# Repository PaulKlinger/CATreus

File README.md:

# CATreus

A wireless keyboard based on the Keyboardio Atreus.

* NRF54L15 Bluetooth SoC (HolyIOT module)
* NPM1300 PMIC for battery management
* 14500 li-ion battery (900mAh)
* 128x64 OLED display (SSD13060based)
* 4 status LEDs, 1 charge LED
* 3D printed [case](/case)
* custom [firmware](/kbd_firmware)
* Kailh Midnight Pro Silent Switches
* MAO profile keycaps ([from Aliexpress](https://www.aliexpress.com/item/1005008664883621.html))
* cat animations by John William Bond (u/Kaimatten), [original video](https://www.reddit.com/r/PixelArt/comments/hoxd95/1_minute_of_1_bit_cat_animations)

Key layout is hardcoded in the firware, I'm using a NEO2 based layout.

## Notes

Programmed via the 5 holes on the top next to the leds, using a custom pogo pin connector.
Spacing is 2.54mm, so can just solder pogo pins to a piece of protoboard.
pinout:
```
   NC    RESET   GND
   3V3   SWDIO   SWCLK
```

Wake button is top left of the center 4 buttons, used to wake the keyboard from sleep mode (30min of inactivity).
UI help by pressing wake + H.

CMD & CTRL keys can be swapped with wake + W for use on Windows/Mac this is persisted per bluetooth connection.

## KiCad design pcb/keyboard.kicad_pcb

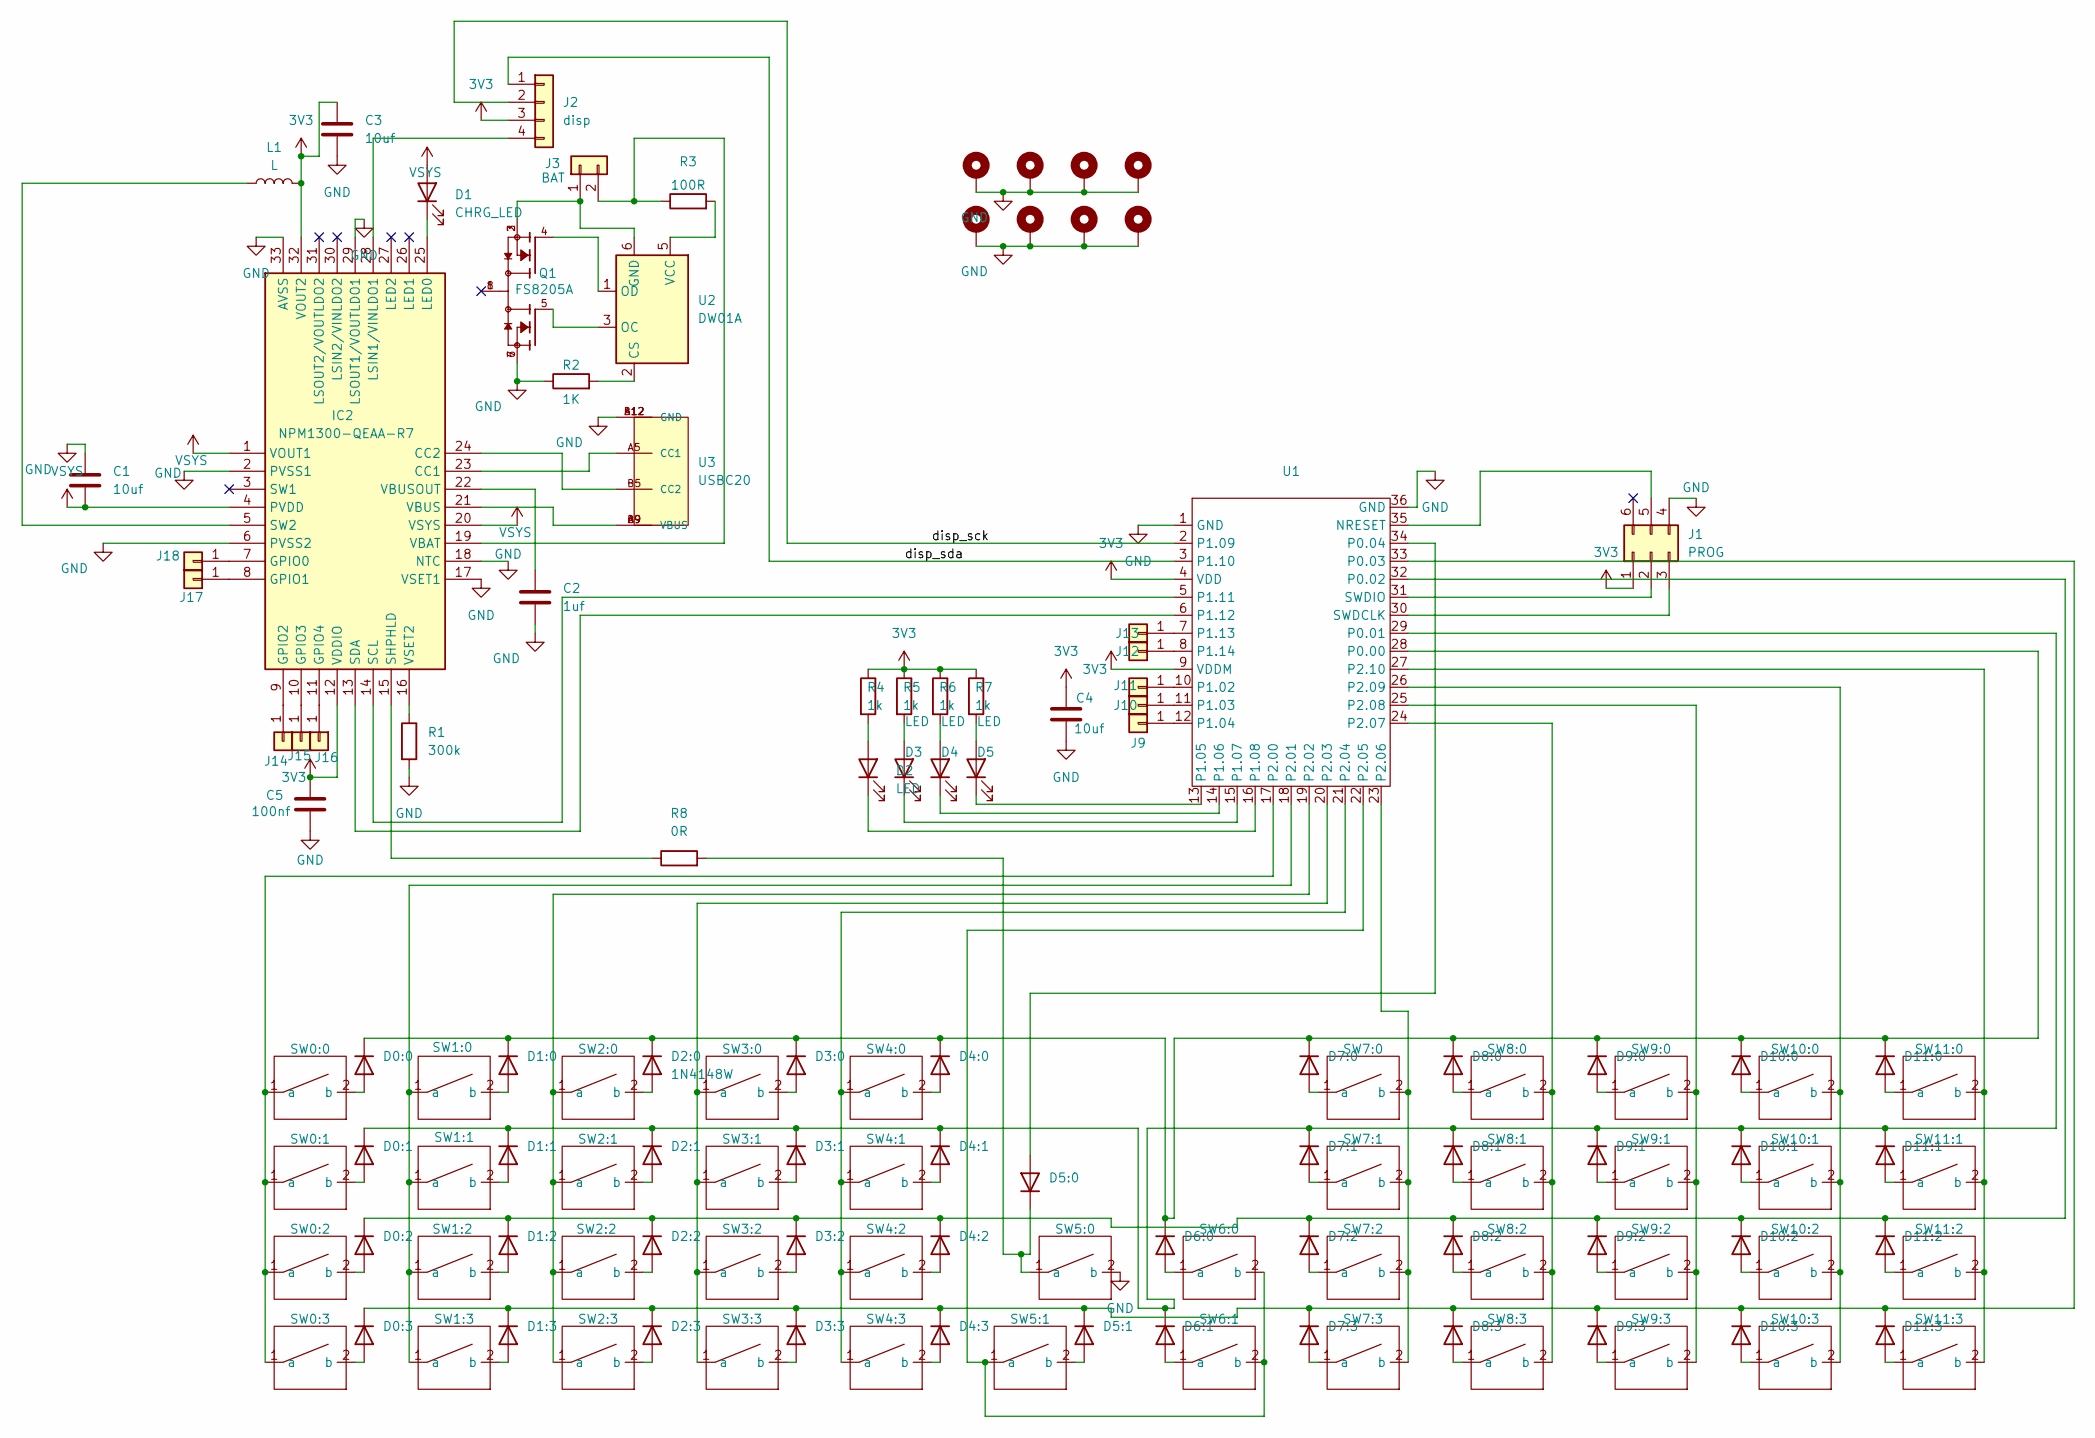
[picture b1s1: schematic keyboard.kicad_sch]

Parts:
C1, C3, C4: 10uf; C_0805_2012Metric_Pad1.18x1.45mm_HandSolder
C2: 1uf; C_0805_2012Metric_Pad1.18x1.45mm_HandSolder
C5: 100nf; C_0805_2012Metric_Pad1.18x1.45mm_HandSolder
D0:0, D0:1, D0:2, D0:3, D1:0, D1:1, D1:2, D1:3, D2:1, D2:2, D2:3, D3:0, D3:1, D3:2, D3:3, D4:0, D4:1, D4:2, D4:3, D5:0, D5:1, D6:0, D6:1, D7:0, D7:1, D7:2, D7:3, D8:0, D8:1, D8:2, D8:3, D9:0, D9:1, D9:2, D9:3, D10:0, D10:1, D10:2, D10:3, D11:0, D11:1, D11:2, D11:3: Nexperia_CFP3_SOD-123W
D1: CHRG_LED; LED_0805_2012Metric_Pad1.15x1.40mm_HandSolder
D2, D3, D4, D5: LED; LED_0805_2012Metric_Pad1.15x1.40mm_HandSolder
D2:0: 1N4148W; D_SOD-123
H1, H2, H3, H4, H5, H6, H7, H8: MountingHole_Pad; MountingHole_2.2mm_M2_DIN965_Pad
IC2: NPM1300-QEAA-R7; QFN50P500X500X90-33N; Mouser Part Number 949-NPM1300-QEAA-R7
J1: PROG; SWD_PROG_5pin
J2: disp; PinHeader_1x04_P2.54mm_Vertical
J3: BAT; PinHeader_1x02_P2.54mm_Vertical
J9, J10, J11, J12, J13, J14, J15, J16, J17, J18: Conn_01x01; SolderWirePad_1x01_SMD_1x2mm
L1: L; L_1008_2520Metric_Pad1.43x2.20mm_HandSolder
Q1: FS8205A; SOP65P640X120-8N; PARTREV 1.7
R1: 300k; R_0805_2012Metric_Pad1.20x1.40mm_HandSolder
R2: 1K; R_0805_2012Metric_Pad1.20x1.40mm_HandSolder
R3: 100R; R_0805_2012Metric_Pad1.20x1.40mm_HandSolder
R4, R5, R6, R7: 1k; R_0805_2012Metric_Pad1.20x1.40mm_HandSolder
R8: 0R; R_0805_2012Metric_Pad1.20x1.40mm_HandSolder
SW0:0, SW0:1, SW0:2, SW0:3, SW1:0, SW1:1, SW1:2, SW1:3, SW2:0, SW2:1, SW2:2, SW2:3, SW3:0, SW3:1, SW3:2, SW3:3, SW4:0, SW4:1, SW4:2, SW4:3, SW5:0, SW5:1, SW6:0, SW6:1, SW7:0, SW7:1, SW7:2, SW7:3, SW8:0, SW8:1, SW8:2, SW8:3, SW9:0, SW9:1, SW9:2, SW9:3, SW10:0, SW10:1, SW10:2, SW10:3, SW11:0, SW11:1, SW11:2, SW11:3: SW_Cherry_MX_PCB
U1: nrf54l15_holyiot
U2: DW01A; SOT-23-6
U3: USBC20; USBC_6PIN

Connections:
3V3: C3.1, C4.1, C5.1, IC2.12 (VDDIO), IC2.32 (VOUT2), J1.1, J2.3, L1.2, R4.1, R5.1, R6.1, R7.1, U1.4 (VDD), U1.9 (VDDM)
/disp_sck: J2.2, U1.2 (P1.09)
/disp_sda: J2.1, U1.3 (P1.10)
GND: C1.1, C2.2, C3.2, C4.2, C5.2, H1.1, H2.1, H3.1, H4.1, H5.1, H6.1, H7.1, H8.1, IC2.2 (PVSS1), IC2.6 (PVSS2), IC2.17 (VSET1), IC2.18 (NTC), IC2.29 (LSOUT1/VOUTLDO1), IC2.33 (AVSS), J1.4, Q1.6, Q1.7, R1.2, R2.1, SW5:0.2 (b), U1.1 (GND), U1.36 (GND), U3.A12 (GND), U3.B12 (GND)
unnamed: D0:0.2 (A), SW0:0.2 (b)
unnamed: D0:0.1 (K), D1:0.1 (K), D2:0.1 (K), D3:0.1 (K), D4:0.1 (K), D6:0.1 (K), D7:0.1 (K), D8:0.1 (K), D9:0.1 (K), D10:0.1 (K), D11:0.1 (K), U1.28 (P0.00)
unnamed: D0:1.2 (A), SW0:1.2 (b)
unnamed: D0:1.1 (K), D1:1.1 (K), D2:1.1 (K), D3:1.1 (K), D4:1.1 (K), D6:1.1 (K), D7:1.1 (K), D8:1.1 (K), D9:1.1 (K), D10:1.1 (K), D11:1.1 (K), U1.29 (P0.01)
unnamed: D0:2.2 (A), SW0:2.2 (b)
unnamed: D0:2.1 (K), D1:2.1 (K), D2:2.1 (K), D3:2.1 (K), D4:2.1 (K), D7:2.1 (K), D8:2.1 (K), D9:2.1 (K), D10:2.1 (K), D11:2.1 (K), U1.32 (P0.02)
unnamed: D0:3.2 (A), SW0:3.2 (b)
unnamed: D0:3.1 (K), D1:3.1 (K), D2:3.1 (K), D3:3.1 (K), D4:3.1 (K), D5:1.1 (K), D7:3.1 (K), D8:3.1 (K), D9:3.1 (K), D10:3.1 (K), D11:3.1 (K), U1.33 (P0.03)
unnamed: D1.1 (K), IC2.25 (LED0)
unnamed: D1:0.2 (A), SW1:0.2 (b)
unnamed: D1:1.2 (A), SW1:1.2 (b)
unnamed: D1:2.2 (A), SW1:2.2 (b)
unnamed: D1:3.2 (A), SW1:3.2 (b)
unnamed: D2.2 (A), R4.2
unnamed: D2.1 (K), U1.16 (P1.08)
unnamed: D2:0.2 (A), SW2:0.2 (b)
unnamed: D2:1.2 (A), SW2:1.2 (b)
unnamed: D2:2.2 (A), SW2:2.2 (b)
unnamed: D2:3.2 (A), SW2:3.2 (b)
unnamed: D3.2 (A), R5.2
unnamed: D3.1 (K), U1.15 (P1.07)
unnamed: D3:0.2 (A), SW3:0.2 (b)
unnamed: D3:1.2 (A), SW3:1.2 (b)
unnamed: D3:2.2 (A), SW3:2.2 (b)
unnamed: D3:3.2 (A), SW3:3.2 (b)
unnamed: D4.2 (A), R6.2
unnamed: D4.1 (K), U1.14 (P1.06)
unnamed: D4:0.2 (A), SW4:0.2 (b)
unnamed: D4:1.2 (A), SW4:1.2 (b)
unnamed: D4:2.2 (A), SW4:2.2 (b)
unnamed: D4:3.2 (A), SW4:3.2 (b)
unnamed: D5.2 (A), R7.2
unnamed: D5.1 (K), U1.13 (P1.05)
unnamed: D5:0.2 (A), U1.34 (P0.04)
unnamed: D5:0.1 (K), R8.2, SW5:0.1 (a)
unnamed: D5:1.2 (A), SW5:1.2 (b)
unnamed: D6:0.2 (A), SW6:0.1 (a)
unnamed: D6:1.2 (A), SW6:1.1 (a)
unnamed: D7:0.2 (A), SW7:0.1 (a)
unnamed: D7:1.2 (A), SW7:1.1 (a)
unnamed: D7:2.2 (A), SW7:2.1 (a)
unnamed: D7:3.2 (A), SW7:3.1 (a)
unnamed: D8:0.2 (A), SW8:0.1 (a)
unnamed: D8:1.2 (A), SW8:1.1 (a)
unnamed: D8:2.2 (A), SW8:2.1 (a)
unnamed: D8:3.2 (A), SW8:3.1 (a)
unnamed: D9:0.2 (A), SW9:0.1 (a)
unnamed: D9:1.2 (A), SW9:1.1 (a)
unnamed: D9:2.2 (A), SW9:2.1 (a)
unnamed: D9:3.2 (A), SW9:3.1 (a)
unnamed: D10:0.2 (A), SW10:0.1 (a)
unnamed: D10:1.2 (A), SW10:1.1 (a)
unnamed: D10:2.2 (A), SW10:2.1 (a)
unnamed: D10:3.2 (A), SW10:3.1 (a)
unnamed: D11:0.2 (A), SW11:0.1 (a)
unnamed: D11:1.2 (A), SW11:1.1 (a)
unnamed: D11:2.2 (A), SW11:2.1 (a)
unnamed: D11:3.2 (A), SW11:3.1 (a)
unnamed: IC2.23 (CC1), U3.A5 (CC1)
unnamed: IC2.24 (CC2), U3.B5 (CC2)
unnamed: IC2.7 (GPIO0), J18.1
unnamed: IC2.8 (GPIO1), J17.1
unnamed: IC2.9 (GPIO2), J14.1
unnamed: IC2.10 (GPIO3), J15.1
unnamed: IC2.11 (GPIO4), J16.1
unnamed: IC2.28 (LSIN1/VINLDO1), J2.4
unnamed: IC2.14 (SCL), U1.5 (P1.11)
unnamed: IC2.13 (SDA), U1.6 (P1.12)
unnamed: IC2.15 (SHPHLD), R8.1
unnamed: IC2.5 (SW2), L1.1
unnamed: IC2.19 (VBAT), J3.2, R3.1
unnamed: IC2.21 (VBUS), U3.A9 (VBUS), U3.B9 (VBUS)
unnamed: C2.1, IC2.22 (VBUSOUT)
unnamed: IC2.16 (VSET2), R1.1
unnamed: J1.2, U1.31 (SWDIO)
unnamed: J1.3, U1.30 (SWDCLK)
unnamed: J1.5, U1.35 (NRESET)
unnamed: J3.1, Q1.2, Q1.3, U2.6 (GND)
unnamed: J9.1, U1.12 (P1.04)
unnamed: J10.1, U1.11 (P1.03)
unnamed: J11.1, U1.10 (P1.02)
unnamed: J12.1, U1.8 (P1.14)
unnamed: J13.1, U1.7 (P1.13)
unnamed: SW0:0.1 (a), SW0:1.1 (a), SW0:2.1 (a), SW0:3.1 (a), U1.17 (P2.00)
unnamed: SW1:0.1 (a), SW1:1.1 (a), SW1:2.1 (a), SW1:3.1 (a), U1.18 (P2.01)
unnamed: SW2:0.1 (a), SW2:1.1 (a), SW2:2.1 (a), SW2:3.1 (a), U1.19 (P2.02)
unnamed: SW3:0.1 (a), SW3:1.1 (a), SW3:2.1 (a), SW3:3.1 (a), U1.20 (P2.03)
unnamed: SW4:0.1 (a), SW4:1.1 (a), SW4:2.1 (a), SW4:3.1 (a), U1.21 (P2.04)
unnamed: SW5:1.1 (a), SW6:0.2 (b), SW6:1.2 (b), U1.22 (P2.05)
unnamed: SW7:0.2 (b), SW7:1.2 (b), SW7:2.2 (b), SW7:3.2 (b), U1.23 (P2.06)
unnamed: SW8:0.2 (b), SW8:1.2 (b), SW8:2.2 (b), SW8:3.2 (b), U1.24 (P2.07)
unnamed: SW9:0.2 (b), SW9:1.2 (b), SW9:2.2 (b), SW9:3.2 (b), U1.25 (P2.08)
unnamed: SW10:0.2 (b), SW10:1.2 (b), SW10:2.2 (b), SW10:3.2 (b), U1.26 (P2.09)
unnamed: SW11:0.2 (b), SW11:1.2 (b), SW11:2.2 (b), SW11:3.2 (b), U1.27 (P2.10)
unnamed: R2.2, U2.2 (CS)
unnamed: Q1.5, U2.3 (OC)
unnamed: Q1.4, U2.1 (OD)
unnamed: R3.2, U2.5 (VCC)
VSYS: C1.2, D1.2 (A), IC2.1 (VOUT1), IC2.4 (PVDD), IC2.20 (VSYS)

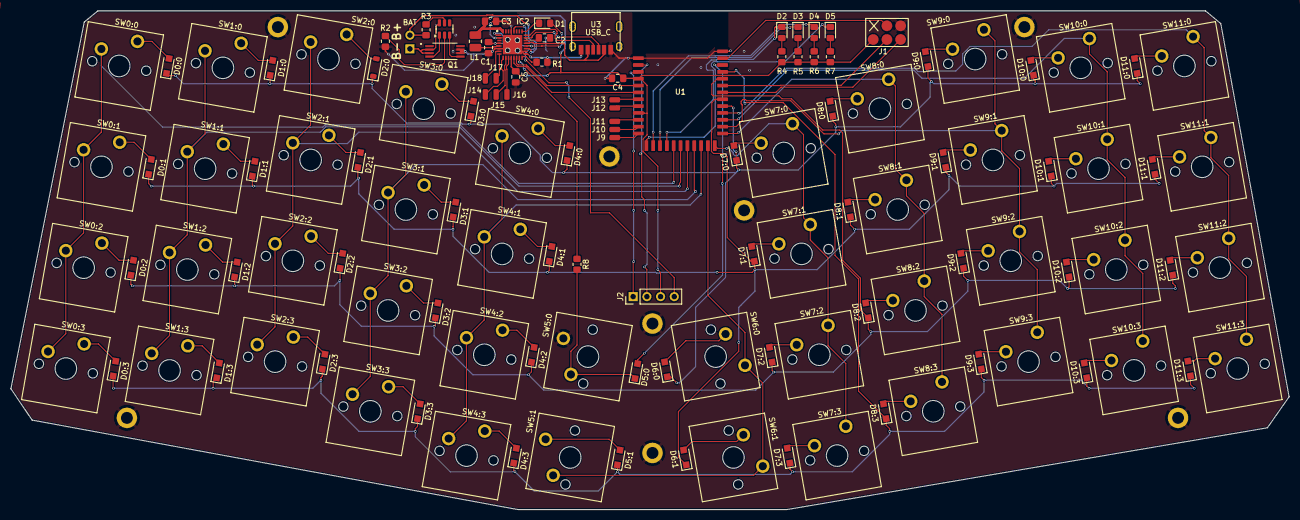
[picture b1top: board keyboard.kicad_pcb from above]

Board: 2 copper layers, 237.1 x 92.5 mm, 133 parts (1 on the bottom side), 103 nets.

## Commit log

2025-05-03 initial commit, PoC for bluetooth HID & SSD1306 display
2025-05-03 wip kicad pcb
2025-05-03 wip pixel face anim (based on alexandr kiryanov's)
2025-05-04 ~finished schematic, started layout
2025-05-05 v1.0 PCB (jlcpcb order)
2025-05-05 pdf schematic
2025-05-18 custom board, working battery charger & uart logging
2025-05-19 disp ldsw control
2025-05-19 disp stuff
2025-05-21 keyboard matrix reading, wake on interrupt
2025-05-24 full keyboard layout, send hid commands
2025-05-24 ship mode on wake + s, dcdc mode for vregmain, increased uart baud
2025-05-25 bluetooth pairing with passkey (single connection)
2025-05-25 v1 case
2025-05-25 fix layer_2 row 0 misalignment
2025-05-26 basic ui framework, wip
2025-05-26 finished (?) case
2025-05-26 only send hid/ui message on changes
2025-05-26 led control, advertising animation, various tweaks
2025-05-26 handle repairing, tweaks. Currently works on android/windows but not mac :(
2025-05-26 use hids api, WORKS ON MAC FINALLY!!
2025-05-26 different sleep timeout while advertising, hacky mandelbrot app
2025-05-26 bugfix in layout, only change layers from layer 0 (not sure I'll keep that)
2025-05-26 add sleep to ensure ui thread has suspended
2025-05-26 case for first fully assembled version
2025-05-27 keep track of current/last key state in key_matrix, new help page, option to swap ctrl & cmd
2025-05-27 keq function for key compare
2025-05-27 handle layer switches more gracefully by keeping track of active layer when keys were pressed, correct alt key mapping
2025-05-27 apps menu, cleanup
2025-05-28 disable key sending during application
2025-05-28 cleanup
2025-05-28 go to sleep if keys are constantly pressed to avoid battery drain
2025-05-31 use keypad for + (fewer modifier conflicts)
2025-05-31 wakeup animation, increase i2c speed
2025-05-31 add notebook to convert animation frames to displaybuffer
2025-05-31 try to make display les flickery (not sure it did anything)
2025-05-31 more animations
2025-05-31 try to make ui more responsive
2025-05-31 workspace
2025-05-31 nvs for n boot count, wip storing cmd/ctrl state (not working yet)
2025-06-01 fixed ctrl/cmd swap config storage
2025-06-01 disable uart logging
2025-06-01 port remaining apps from tinypc
2025-06-01 add animation credit, fix snake startup, cleanup
2025-06-01 add poetry env for anim notebook & pre-commit
2025-06-01 add pre-commit hooks, run formatter on firmware
2025-06-01 tweak display cover
2025-06-01 move/reorg pcb folder
2025-06-01 add readme
2025-06-01 gitignore
2025-06-01 readme, gitignore
2025-06-01 Create LICENSE
2025-06-01 readme
2025-06-01 allow exit from tetris, debounce tweak
2025-06-02 use markdown for readme
2025-06-07 get rid of n_boot counter for flash longevity
2025-06-13 add fuel gauge for battery soc
2025-06-14 central pmic_state
2025-06-14 shorten wake press time
2025-06-14 send battery state
2025-06-14 formatting
2025-06-14 minor fixes
